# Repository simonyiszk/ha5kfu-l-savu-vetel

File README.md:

# ha5kfu-l-savu-vetel
Az L sávú műholdvételi projekthez (jelenleg ELEKTRO-L3) tartozó anyagok

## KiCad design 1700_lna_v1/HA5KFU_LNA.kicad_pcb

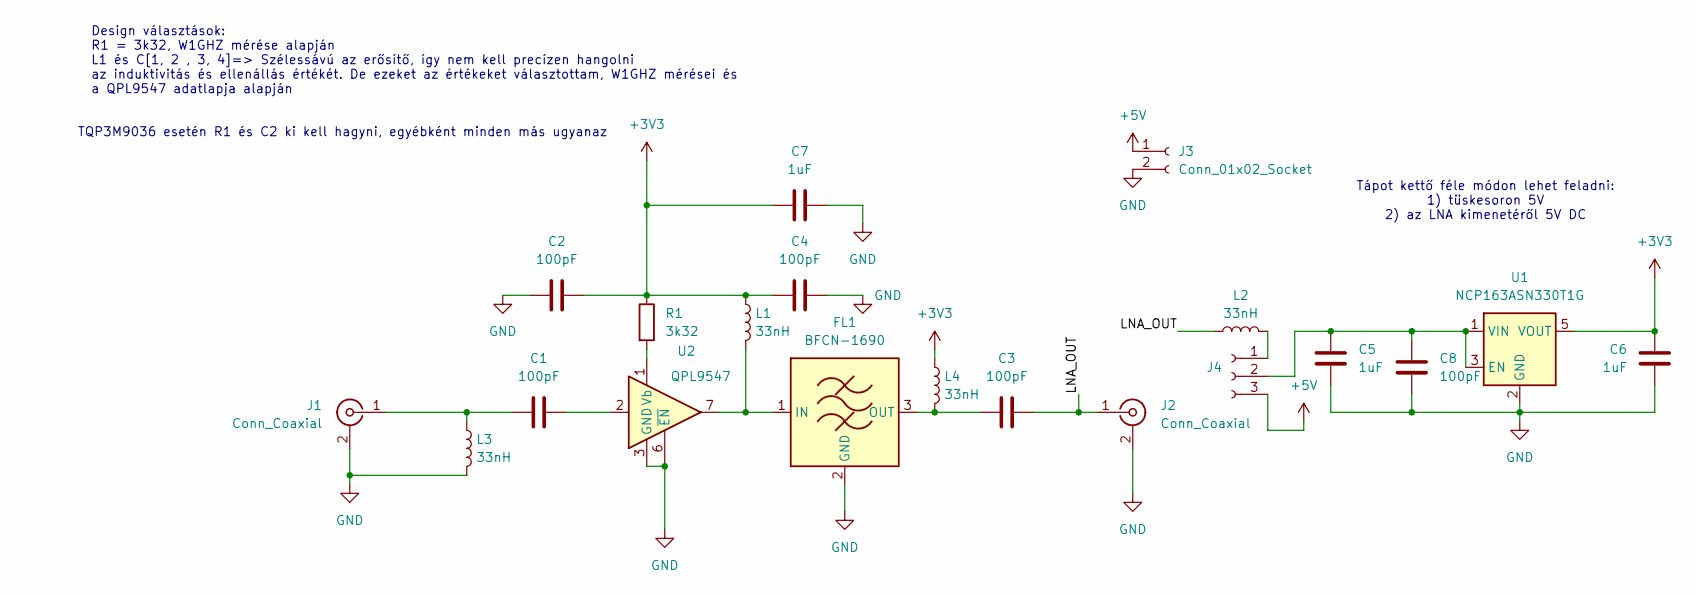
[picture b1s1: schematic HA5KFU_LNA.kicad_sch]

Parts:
C1, C2, C3, C4, C8: 100pF; C_0402_1005Metric_Pad0.74x0.62mm_HandSolder
C5, C6, C7: 1uF; C_0603_1608Metric_Pad1.08x0.95mm_HandSolder
FL1: BFCN-1690; Filter_Mini-Circuits_FV1206-1
J1, J2: Conn_Coaxial; SMA_Amphenol_132134_Vertical
J3: Conn_01x02_Socket; PinHeader_1x02_P2.54mm_Vertical
J4: Conn_01x03_Socket; PinHeader_1x03_P2.54mm_Vertical
L1, L2, L3, L4: 33nH; L_0402_1005Metric_Pad0.77x0.64mm_HandSolder
R1: 3k32; R_0402_1005Metric_Pad0.72x0.64mm_HandSolder
U1: NCP163ASN330T1G; SOT-23-5
U2: QPL9547; DFN-8-1EP_2x2mm_P0.5mm_EP0.8x1.6mm

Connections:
+3V3: C2.1, C4.1, C6.1, C7.1, L1.1, L4.1, R1.1, U1.5 (VOUT)
+5V: J3.1, J4.3
/LNA_OUT: C3.2, J2.1 (In), L2.1
GND: C2.2, C4.2, C5.2, C6.2, C7.2, C8.1, FL1.2 (GND), FL1.4 (GND), FL1.5 (GND), FL1.6 (GND), J1.2 (Ext), J2.2 (Ext), J3.2, L3.2, U1.2 (GND), U2.3 (GND), U2.4 (GND), U2.5 (GND), U2.6 (~EN), U2.8 (GND), U2.9 (GND)
unnamed: C1.2, U2.2
unnamed: FL1.1 (IN), L1.2, U2.7
unnamed: C3.1, FL1.3 (OUT), L4.2
unnamed: C1.1, J1.1 (In), L3.1
unnamed: J4.1, L2.2
unnamed: C5.1, C8.2, J4.2, U1.1 (VIN), U1.3 (EN)
unnamed: R1.2, U2.1 (Vb)

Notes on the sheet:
TQP3M9036 esetén R1 és C2 ki kell hagyni, egyébként minden más ugyanaz
Design választások: R1 = 3k32, W1GHZ mérése alapján L1 és C[1, 2 , 3, 4]=> Szélessávú az erősítő, így nem kell precízen hangolni az induktivitás és ellenállás értékét. De ezeket az értékeket választottam, W1GHZ mérései és a QPL9547 adatlapja alapján
Tápot kettő féle módon lehet feladni: 1) tüskesoron 5V 2) az LNA kimenetéről 5V DC

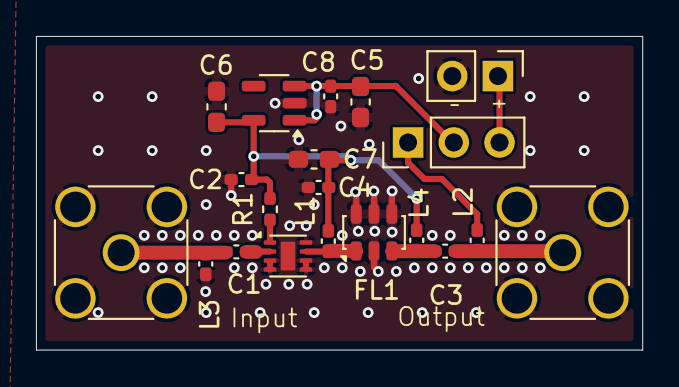
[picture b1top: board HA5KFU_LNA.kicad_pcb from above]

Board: 2 copper layers, 33.7 x 17.4 mm, 20 parts (0 on the bottom side), 11 nets.

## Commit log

2025-07-31 Parabolatartó bilincs tervei
2025-07-31 Primersugárzó tervei
2025-07-31 Üregrezonátoros szűrő
2025-09-02 LNA
    Low Noise Amplifier for Elektro-L satellite.
2025-09-26 Added BOM, project file
2025-12-08 Added V2 of LNA
    *Changed coplanar waveguide to microstrip trasmissionline structure
    *Changed Filter footprint to combined 70cm/L band footprint
    *Increased layer count from 2 to 4
2026-03-23 Added extra vias and power source selector
2026-03-27 refactor(lna_v2): prettify stitching vias
2026-04-01 Changed transmission line parameters
    Changed transmission line width and ground plane to trace distance to better fit reduce parasitic capacitance.
2026-04-09 Removed via from pad
2026-04-12 Update 1700 filter v2
2026-05-28 Adjusted 2 layer PCB design
